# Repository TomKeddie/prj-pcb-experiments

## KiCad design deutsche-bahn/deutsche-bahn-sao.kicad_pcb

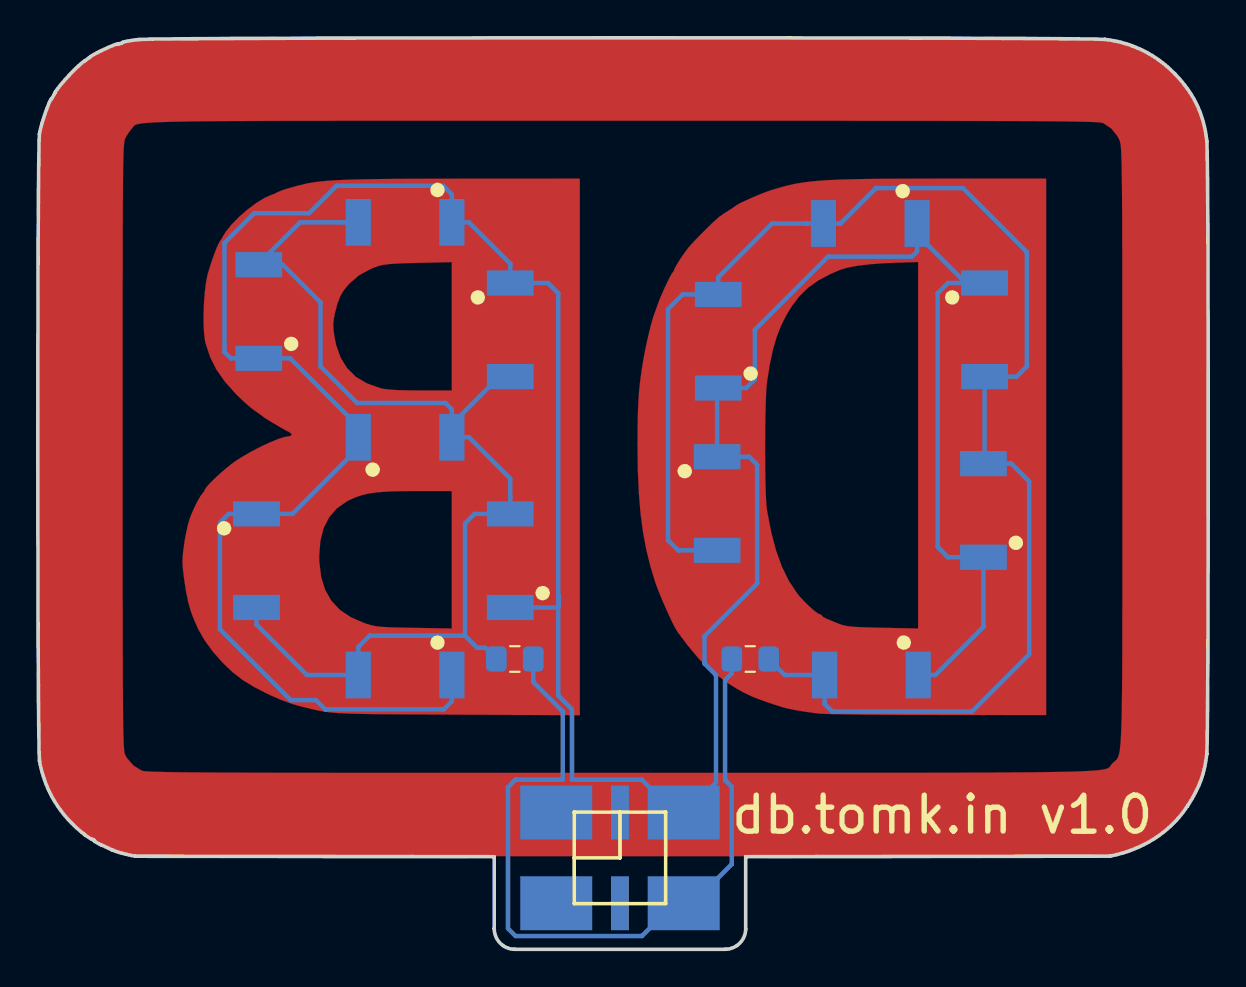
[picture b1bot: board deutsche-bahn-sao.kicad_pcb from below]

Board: 2 copper layers, 65.0 x 50.6 mm, 19 parts (16 on the bottom side), 4 nets.

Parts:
D1, D2, D3, D4, D5, D6, D7, D8, D9, D10, D11, D12, D13: LED; XZM2CYK45WT-9-NOMASK
H1: Logo Copper; 1280px-Deutsche_Bahn_AG-Logo-copper
H2: Logo Mask; 1280px-Deutsche_Bahn_AG-Logo-mask-invert
H3: Logo Silk; 1280px-Deutsche_Bahn_AG-Logo-silk-invert
J1: Conn_02x03_Odd_Even; PinSocket_2x03_P2.54mm_Vertical_SMD_SAO
R1, R2: 47R; C_0805_2012Metric_Pad1.15x1.40mm_HandSolder

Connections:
+3V3: D1.2, D2.2, D3.2, D4.2, D5.2, D6.2, D7.2, D8.2, D9.2, D10.2, D11.2, D12.2, D13.2, J1.5
GND: J1.6, R1.2, R2.2
unnamed: D1.1, D2.1, D4.1, D7.1, D10.1, D11.1, R1.1
unnamed: D3.1, D5.1, D6.1, D8.1, D9.1, D12.1, D13.1, R2.1

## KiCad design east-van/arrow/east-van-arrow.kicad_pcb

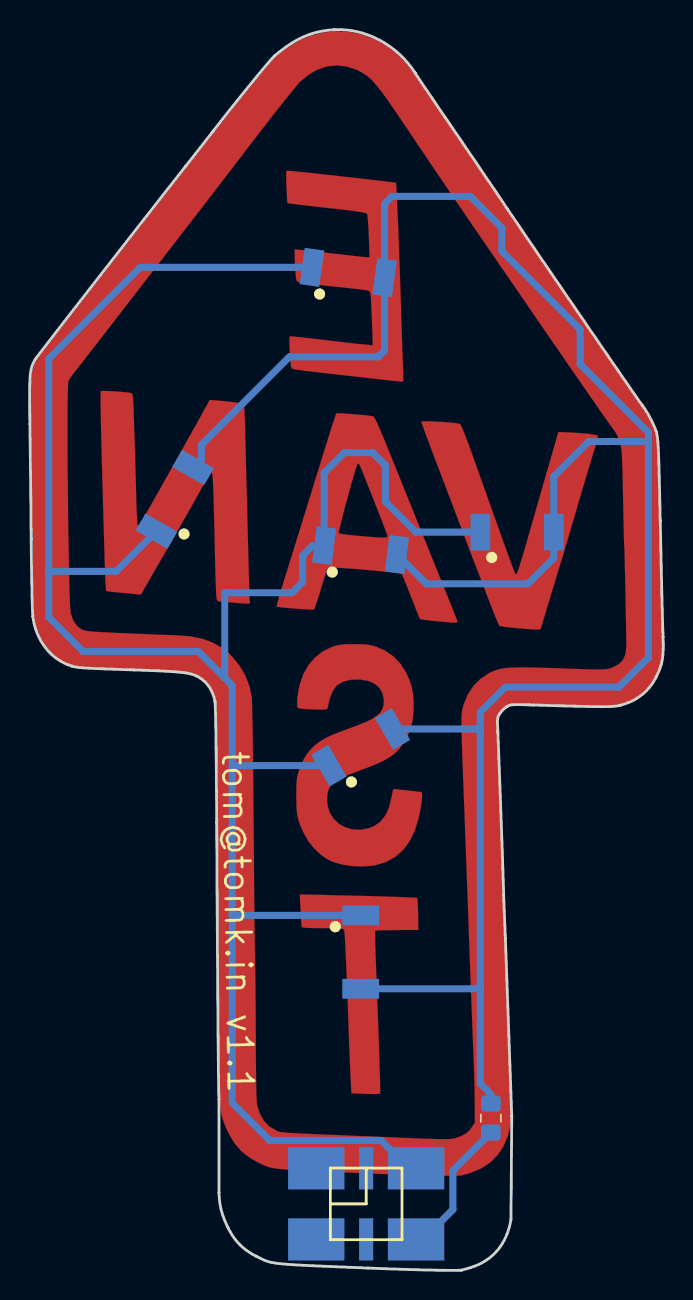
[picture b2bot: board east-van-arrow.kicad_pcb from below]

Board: 2 copper layers, 44.9 x 88.0 mm, 10 parts (8 on the bottom side), 3 nets.

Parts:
D1, D2, D3, D4, D5, D6: LED; XZM2CYK45WT-9-NOMASK
H1: Copper; east-van-arrow-copper
H2: Mask; east-van-arrow-mask-invert
J1: Conn_02x03_Odd_Even; PinSocket_2x03_P2.54mm_Vertical_SMD_SAO
R1: 220R; C_0805_2012Metric_Pad1.15x1.40mm_HandSolder

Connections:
+3V3: D1.2, D2.2, D3.2, D4.2, D5.2, D6.2, J1.5
/CATHODE: D1.1, D2.1, D3.1, D4.1, D5.1, D6.1, R1.1
GND: J1.6, R1.2

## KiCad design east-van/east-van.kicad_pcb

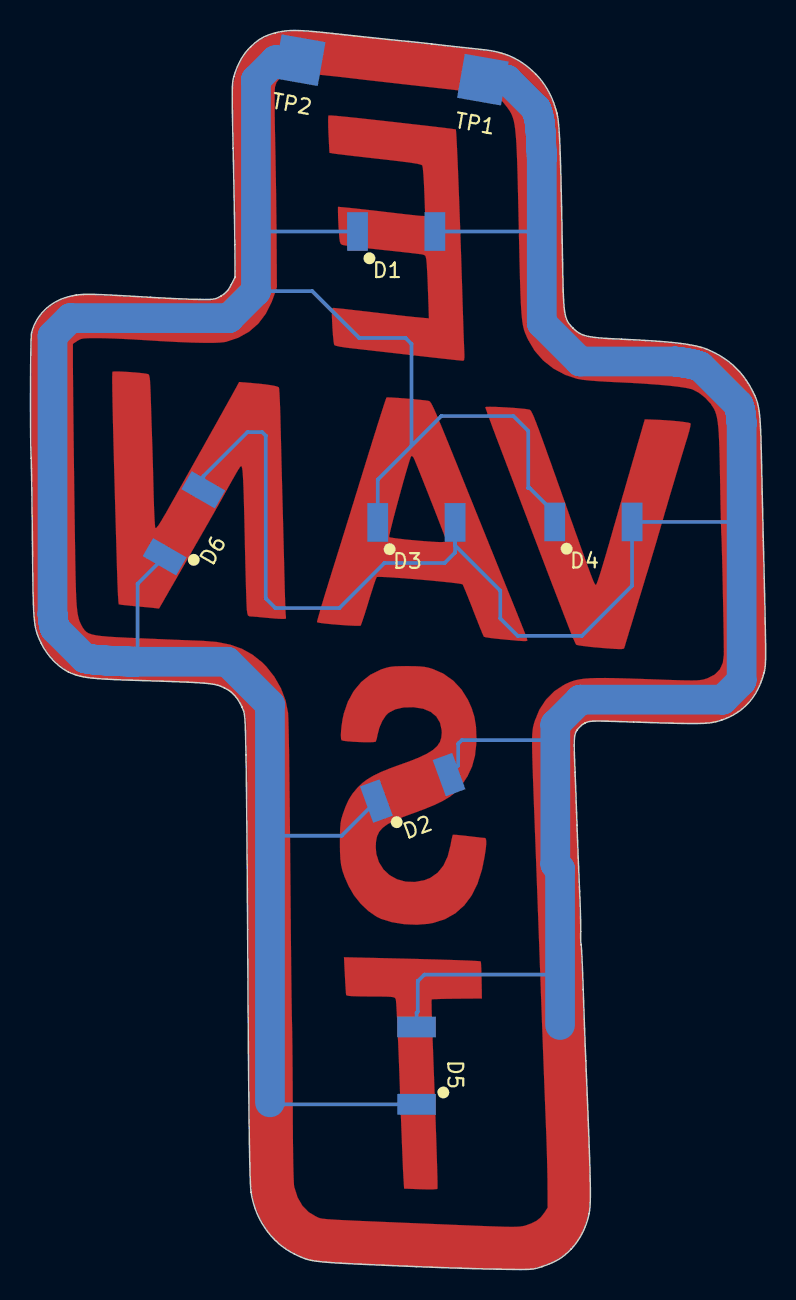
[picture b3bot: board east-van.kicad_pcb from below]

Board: 2 copper layers, 49.4 x 83.3 mm, 11 parts (8 on the bottom side), 2 nets.

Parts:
D1, D2, D3, D4, D5, D6: Device_LED; XZM2CYK45WT-9-NOMASK
H1: mask; east-van-inv-mask
H2: silk; east-van-silk
H3: copper; east-van-copper
TP1, TP2: TestPoint; Measurement_Point_Square-SMD-Pad_Big

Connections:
/A: D1.2, D2.2, D3.2, D4.2, D5.2, D6.2, TP2.1
/C: D1.1, D2.1, D3.1, D4.1, D5.1, D6.1, TP1.1

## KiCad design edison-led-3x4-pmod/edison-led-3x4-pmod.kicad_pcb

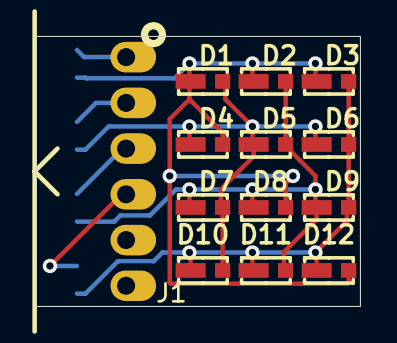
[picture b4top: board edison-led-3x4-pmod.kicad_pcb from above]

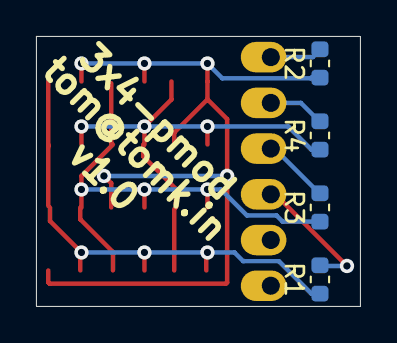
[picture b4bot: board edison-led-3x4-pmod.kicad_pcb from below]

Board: 2 copper layers, 18.0 x 15.0 mm, 17 parts (4 on the bottom side), 8 nets.

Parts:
D1, D2, D3, D4, D5, D6, D7, D8, D9, D10, D11, D12: LED; EDISON-3014
J1: PMOD-1x6-MALE; PMOD_1X6_PTH_RA_PLUG
R1, R2, R3, R4: 47R; R_0603_1608Metric

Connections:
D0: D1.2, D2.2, D3.2, D4.1, D8.1, D12.1, R2.1
D1: D1.1, D4.2, D5.2, D6.2, D7.1, D10.1, R4.1
D2: D2.1, D5.1, D7.2, D8.2, D9.2, D11.1, R3.1
D3: D3.1, D6.1, D9.1, D10.2, D11.2, D12.2, R1.1
unnamed: J1.1, R2.2
unnamed: J1.2, R4.2
unnamed: J1.3, R3.2
unnamed: J1.4, R1.2

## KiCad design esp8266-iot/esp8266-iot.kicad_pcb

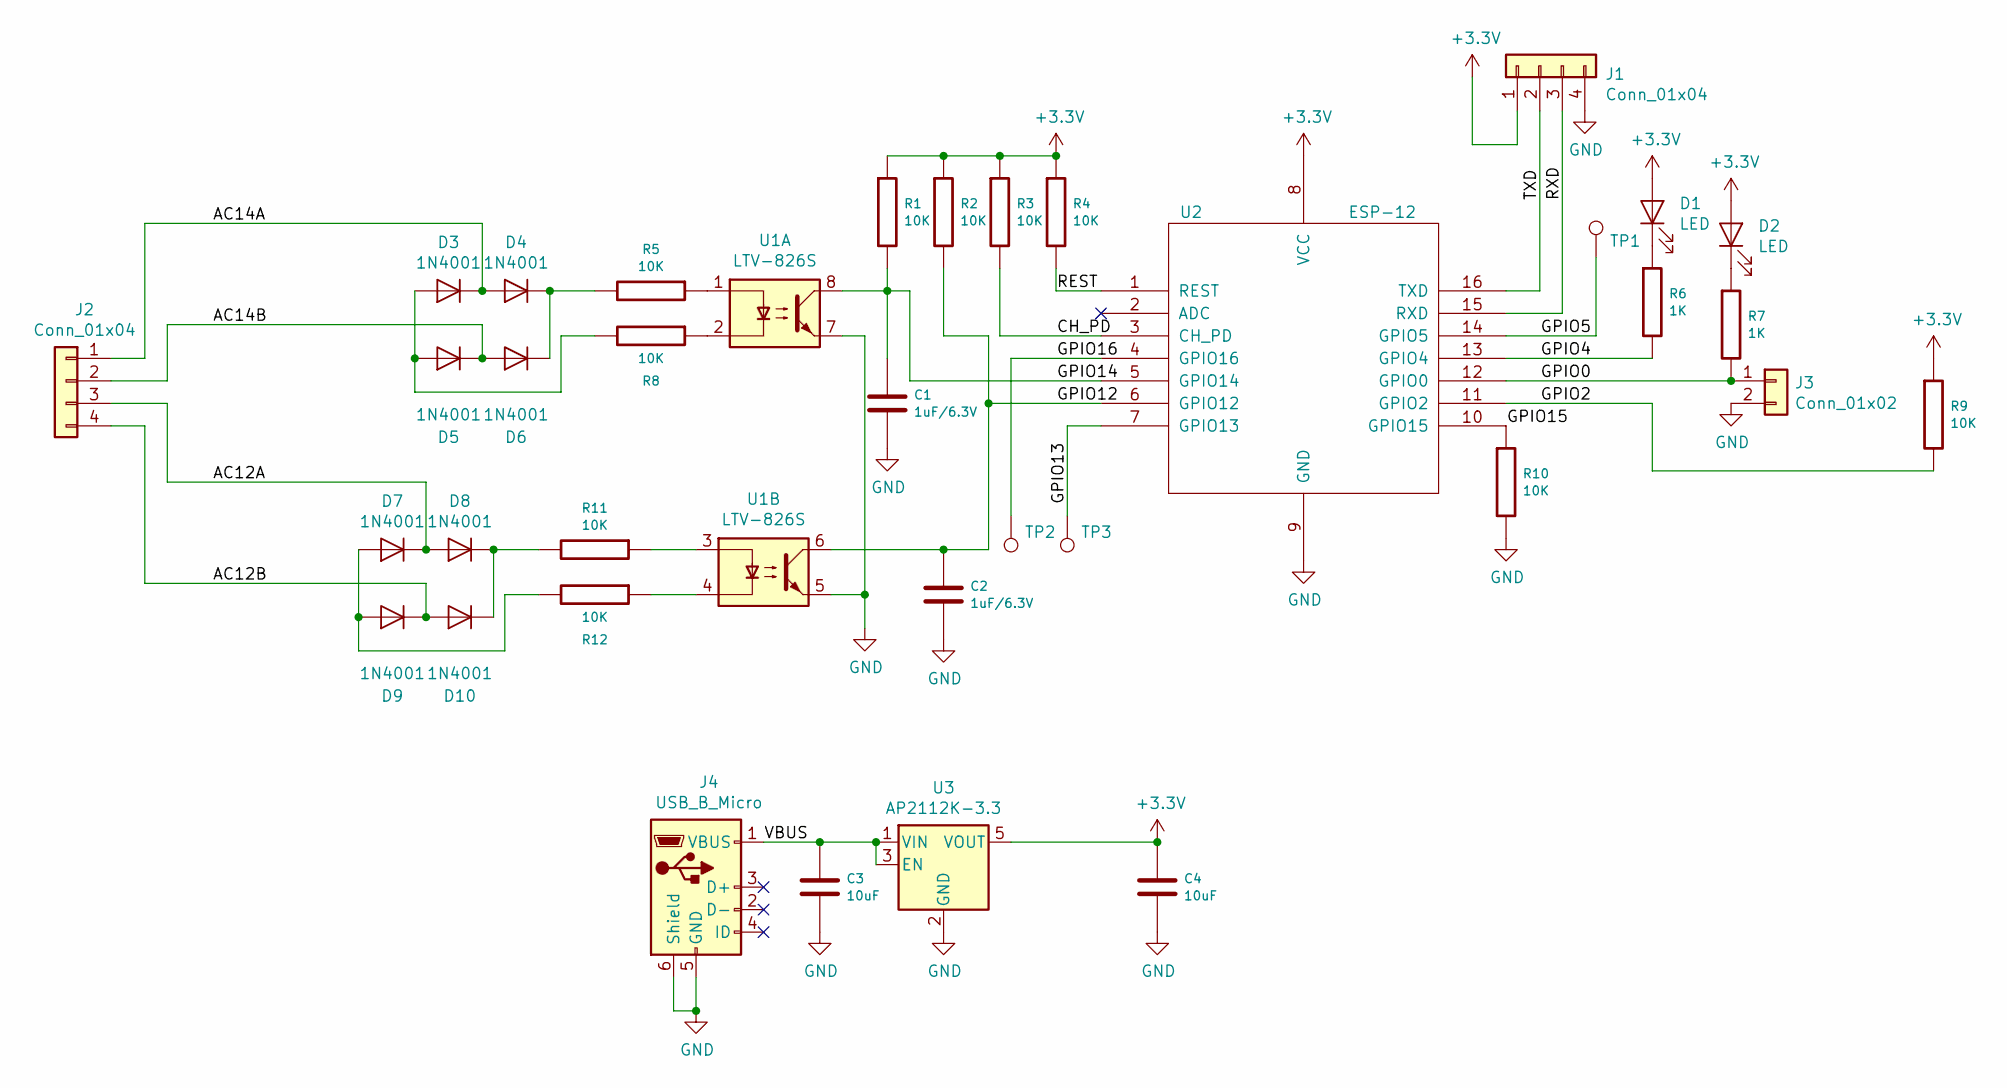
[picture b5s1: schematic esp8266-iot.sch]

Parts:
C1, C2: 1uF/6.3V; C_1206_3216Metric
C3, C4: 10uF; C_1206_3216Metric
D1, D2: LED; LED_0805_2012Metric
D3, D4, D5, D6, D7, D8, D9, D10: 1N4001; D_SMA; Digikey 641-1156-1-ND
J1: Conn_01x04; PinHeader_1x04_P2.54mm_Vertical
J2: Conn_01x04; PhoenixContact_MC_1,5_4-G-5.08_1x04_P5.08mm_Horizontal
J3: Conn_01x02; PinHeader_1x02_P2.54mm_Vertical
J4: USB_B_Micro; USB_MICRO_TAOBAO_SMD_PTH
R1, R2, R3, R4, R5, R8, R9, R10, R11, R12: 10K; C_0805_2012Metric
R6, R7: 1K; C_0805_2012Metric
TP1, TP2, TP3: TestPoint; TestPoint_Pad_D3.0mm
U1: LTV-826S; DIP-8_W8.89mm_SMDSocket_LongPads
U2: ESP-12; ESP-12E_SMD
U3: AP2112K-3.3; SOT-23-5

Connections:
+3V3: C4.1, D1.2 (A), D2.2 (A), J1.1, R1.1, R2.1, R3.1, R4.1, R9.1, U2.8 (VCC), U3.5 (VOUT)
/AC12A: D7.1 (K), D8.2 (A), J2.3
/AC12B: D9.1 (K), D10.2 (A), J2.4
/AC14A: D3.1 (K), D4.2 (A), J2.1
/AC14B: D5.1 (K), D6.2 (A), J2.2
/CH_PD: R3.2, U2.3 (CH_PD)
/GPIO0: J3.1, R7.2, U2.12 (GPIO0)
/GPIO2: R9.2, U2.11 (GPIO2)
/GPIO4: R6.2, U2.13 (GPIO4)
/GPIO5: TP1.1, U2.14 (GPIO5)
/GPIO12: C2.1, R2.2, U1.6, U2.6 (GPIO12)
/GPIO13: TP3.1, U2.7 (GPIO13)
/GPIO14: C1.1, R1.2, U1.8, U2.5 (GPIO14)
/GPIO15: R10.1, U2.10 (GPIO15)
/GPIO16: TP2.1, U2.4 (GPIO16)
/REST: R4.2, U2.1 (REST)
/RXD: J1.3, U2.15 (RXD)
/TXD: J1.2, U2.16 (TXD)
/VBUS: C3.1, J4.1 (VBUS), U3.1 (VIN), U3.3 (EN)
GND: C1.2, C2.2, C3.2, C4.2, J1.4, J3.2, J4.5 (GND), J4.6 (Shield), R10.2, U1.5, U1.7, U2.9 (GND), U3.2 (GND)
unnamed: D1.1 (K), R6.1
unnamed: D2.1 (K), R7.1
unnamed: D3.2 (A), D5.2 (A), R8.2
unnamed: D4.1 (K), D6.1 (K), R5.2
unnamed: D7.2 (A), D9.2 (A), R12.2
unnamed: D8.1 (K), D10.1 (K), R11.2
unnamed: R5.1, U1.1
unnamed: R8.1, U1.2
unnamed: R11.1, U1.3
unnamed: R12.1, U1.4

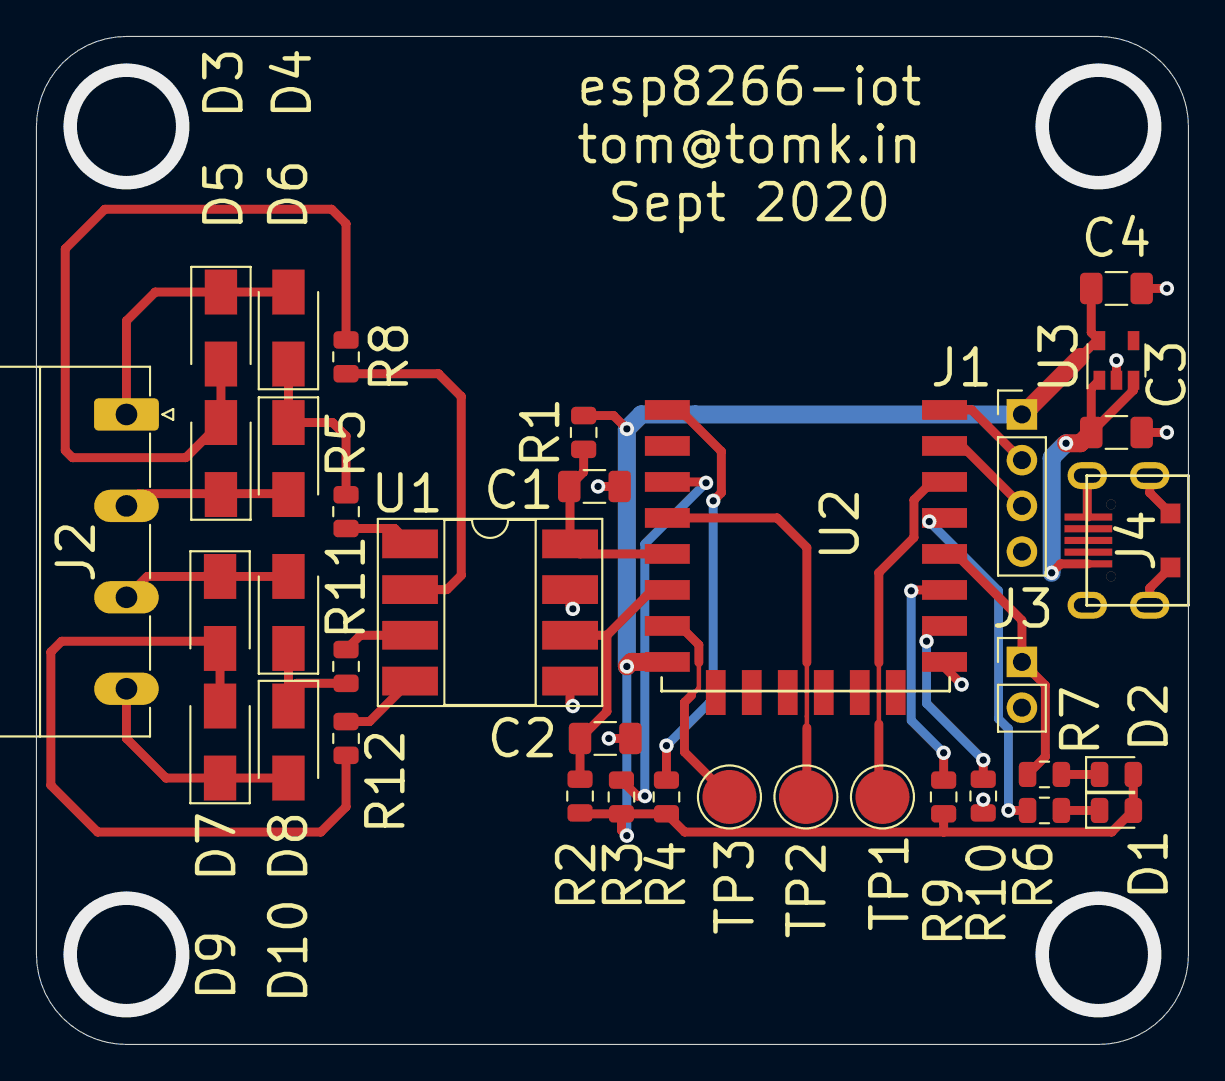
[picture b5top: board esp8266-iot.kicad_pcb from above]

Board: 2 copper layers, 64.0 x 56.0 mm, 36 parts (0 on the bottom side), 30 nets.

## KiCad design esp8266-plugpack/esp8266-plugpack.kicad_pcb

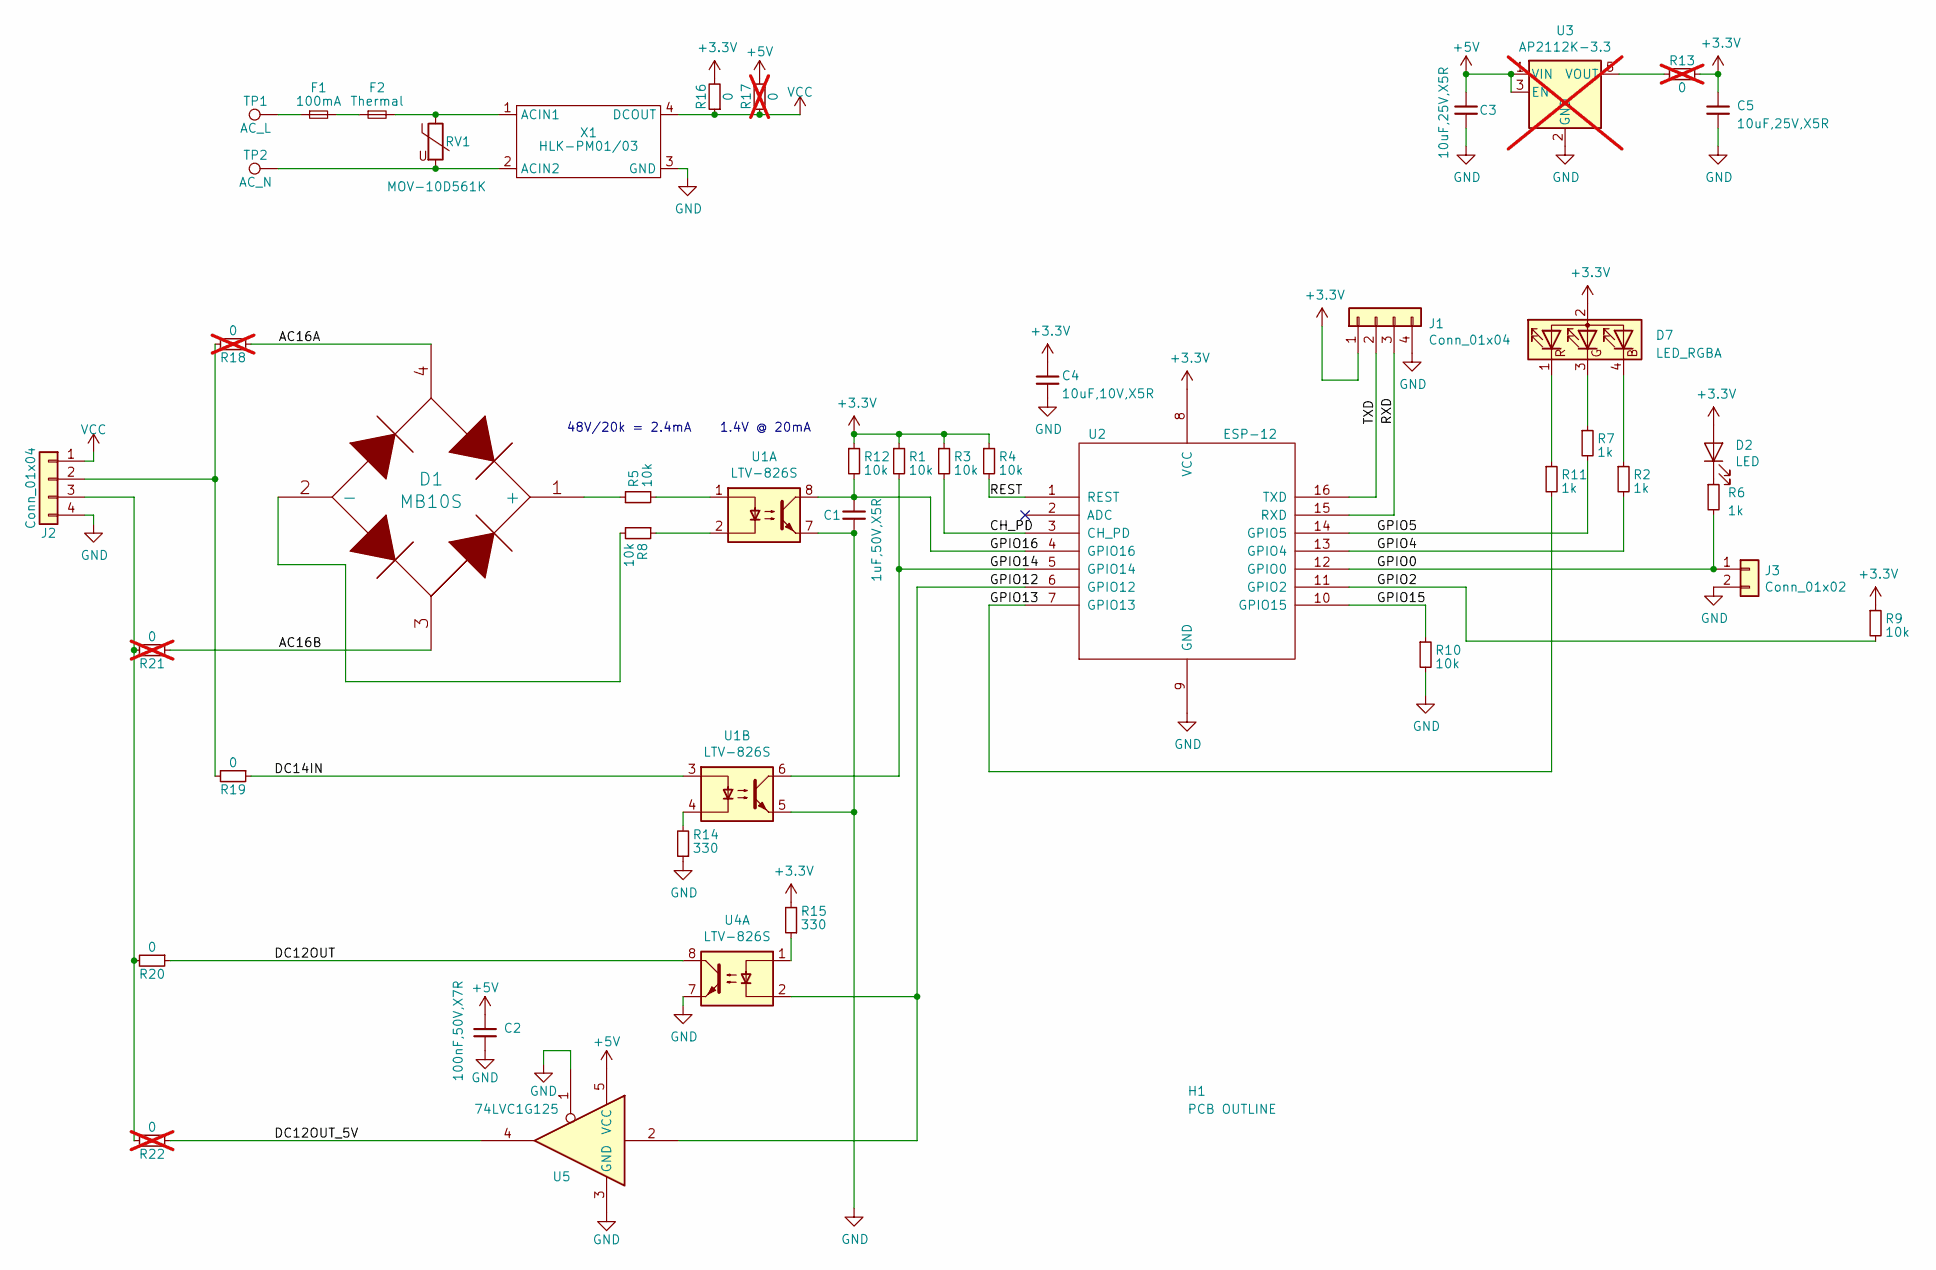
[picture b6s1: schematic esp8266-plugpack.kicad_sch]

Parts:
C1: 1uF,50V,X5R; C_0603_1608Metric; MFGPN CL10A105KB8NNNC; LCSC C15849
C2: 100nF,50V,X7R; C_0603_1608Metric; MFGPN CC0603KRX7R9BB104; LCSC C14663
C3, C5: 10uF,25V,X5R; C_0603_1608Metric; MFGPN CL10A106MA8NRNC; LCSC C96446
C4: 10uF,10V,X5R; C_0603_1608Metric; MFGPN CL10A106KP8NNNC; LCSC C19702
D1: MB10S; Diode_Bridge_MBnnS; LCSC C2488
D2: LED; LED_0805_2012Metric; LCSC C34499
D7: LED_RGBA; LED_D5.0mm-4_RGB
F1: 100mA; Fuse_2410
F2: Thermal; R_Axial_DIN0204_L3.6mm_D1.6mm_P7.62mm_Horizontal
H1: PCB OUTLINE; PCB_ALIEXPRESS_PLUGPACK_1
J1: Conn_01x04; PinHeader_1x04_P2.54mm_Vertical
J2: Conn_01x04; JST_PH_B4B-PH-SM4-TB_1x04-1MP_P2.00mm_Vertical
J3: Conn_01x02; PinHeader_1x02_P2.54mm_Vertical
R1, R3, R4, R5, R8, R9, R10, R12: 10k; R_0603_1608Metric; MFGPN 0603WAF1002T5E; LCSC C25804
R2, R6, R7, R11: 1k; R_0603_1608Metric; MFGPN 0603WAF1001T5E; LCSC C21190
R13, R17, R18, R21, R22: 0; R_0603_1608Metric; MFGPN 0603WAF0000T5E; LCSC C21189; not fitted
R14, R15: 330; R_0603_1608Metric; MFGPN 0603WAF3300T5E; LCSC C23138
R16, R19, R20: 0; R_0603_1608Metric; MFGPN 0603WAF0000T5E; LCSC C21189
RV1: MOV-10D561K; RV_Disc_D12mm_W3.9mm_P7.5mm
TP1: AC_L; TestPoint_Pad_D3.0mm
TP2: AC_N; TestPoint_Pad_D3.0mm
U1, U4: LTV-826S; DIP-8_W8.89mm_SMDSocket_LongPads
U2: ESP-12; ESP-12E_SMD; LCSC C82891
U3: AP2112K-3.3; SOT-23-5; not fitted
U5: 74LVC1G125; SOT-23-5; LCSC C23654
X1: HLK-PM01/03; HLK-PMxx

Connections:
+3.3V: C4.1, C5.1, D2.2 (A), D7.2 (A), J1.1, R1.1, R3.1, R4.1, R9.1, R12.1, R13.2, R15.2, R16.2, U2.8 (VCC)
+5V: C2.1, C3.1, R17.2, U3.1 (VIN), U3.3 (EN), U5.5 (VCC)
/AC16A: D1.4, R18.1
/AC16B: D1.3, R21.1
/CH_PD: R3.2, U2.3 (CH_PD)
/DC12OUT: R20.1, U4.8
/DC12OUT_5V: R22.1, U5.4
/DC14IN: R19.1, U1.3
/GPIO0: J3.1, R6.2, U2.12 (GPIO0)
/GPIO2: R9.2, U2.11 (GPIO2)
/GPIO4: R2.2, U2.13 (GPIO4)
/GPIO5: R7.2, U2.14 (GPIO5)
/GPIO12: U2.6 (GPIO12), U4.2, U5.2
/GPIO13: R11.2, U2.7 (GPIO13)
/GPIO14: R1.2, U1.6, U2.5 (GPIO14)
/GPIO15: R10.1, U2.10 (GPIO15)
/GPIO16: C1.1, R12.2, U1.8, U2.4 (GPIO16)
/REST: R4.2, U2.1 (REST)
/RXD: J1.3, U2.15 (RXD)
/TXD: J1.2, U2.16 (TXD)
GND: C1.2, C2.2, C3.2, C4.2, C5.2, J1.4, J2.4, J3.2, R10.2, R14.1, U1.5, U1.7, U2.9 (GND), U3.2 (GND), U4.7, U5.1, U5.3 (GND), X1.3 (GND)
unnamed: D1.1 (+), R5.1
unnamed: D1.2 (-), R8.2
unnamed: D2.1 (K), R6.1
unnamed: D7.4 (BK), R2.1
unnamed: D7.3 (GK), R7.1
unnamed: D7.1 (RK), R11.1
unnamed: F1.1, TP1.1
unnamed: F1.2, F2.1
unnamed: J2.2, R18.2, R19.2
unnamed: J2.3, R20.2, R21.2, R22.2
unnamed: R5.2, U1.1
unnamed: R8.1, U1.2
unnamed: R14.2, U1.4
unnamed: R15.1, U4.1
unnamed: R13.1, U3.5 (VOUT)
unnamed: F2.2, RV1.1, X1.1 (ACIN1)
unnamed: RV1.2, TP2.1, X1.2 (ACIN2)
VCC: J2.1, R16.1, R17.1, X1.4 (DCOUT)

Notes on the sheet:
48V/20k = 2.4mA
1.4V @ 20mA

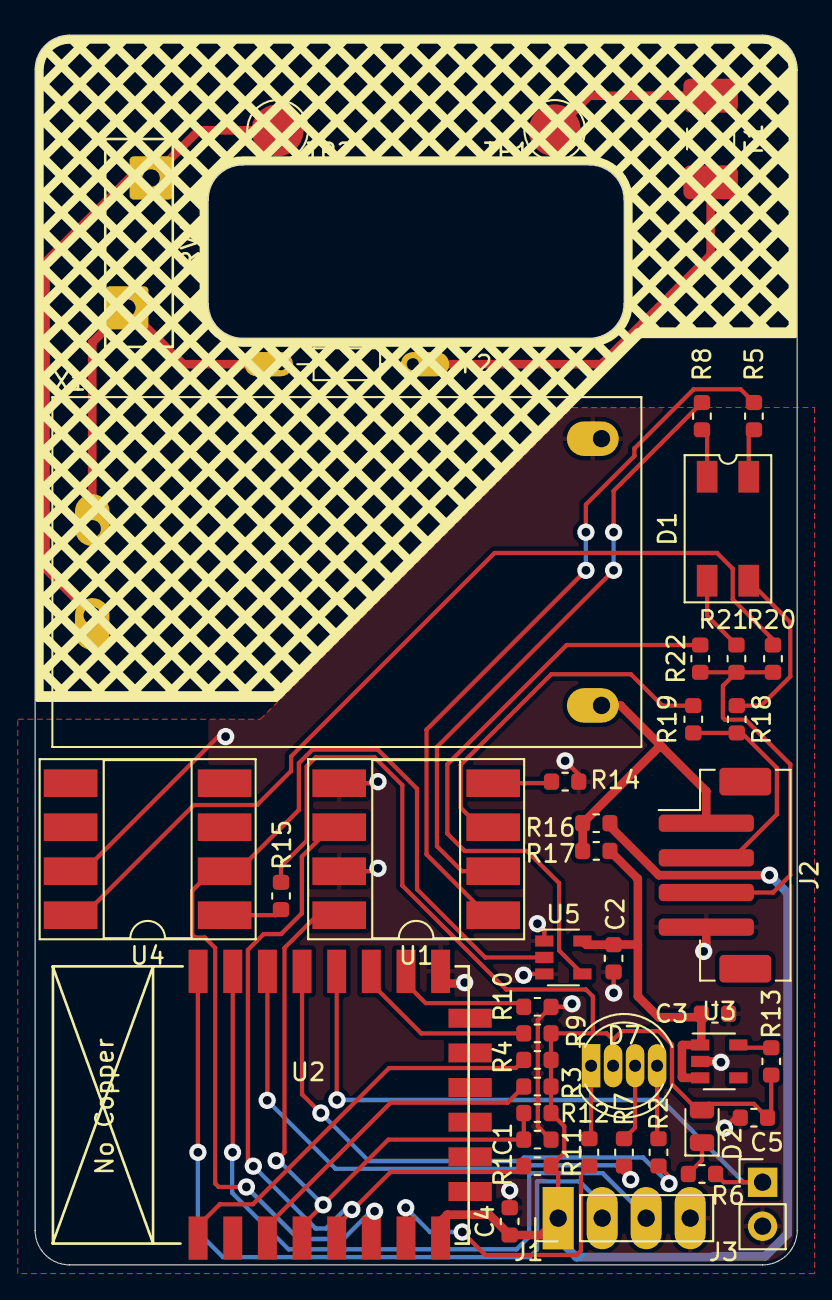
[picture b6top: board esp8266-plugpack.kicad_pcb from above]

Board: 2 copper layers, 44.0 x 71.0 mm, 45 parts (0 on the bottom side), 39 nets.

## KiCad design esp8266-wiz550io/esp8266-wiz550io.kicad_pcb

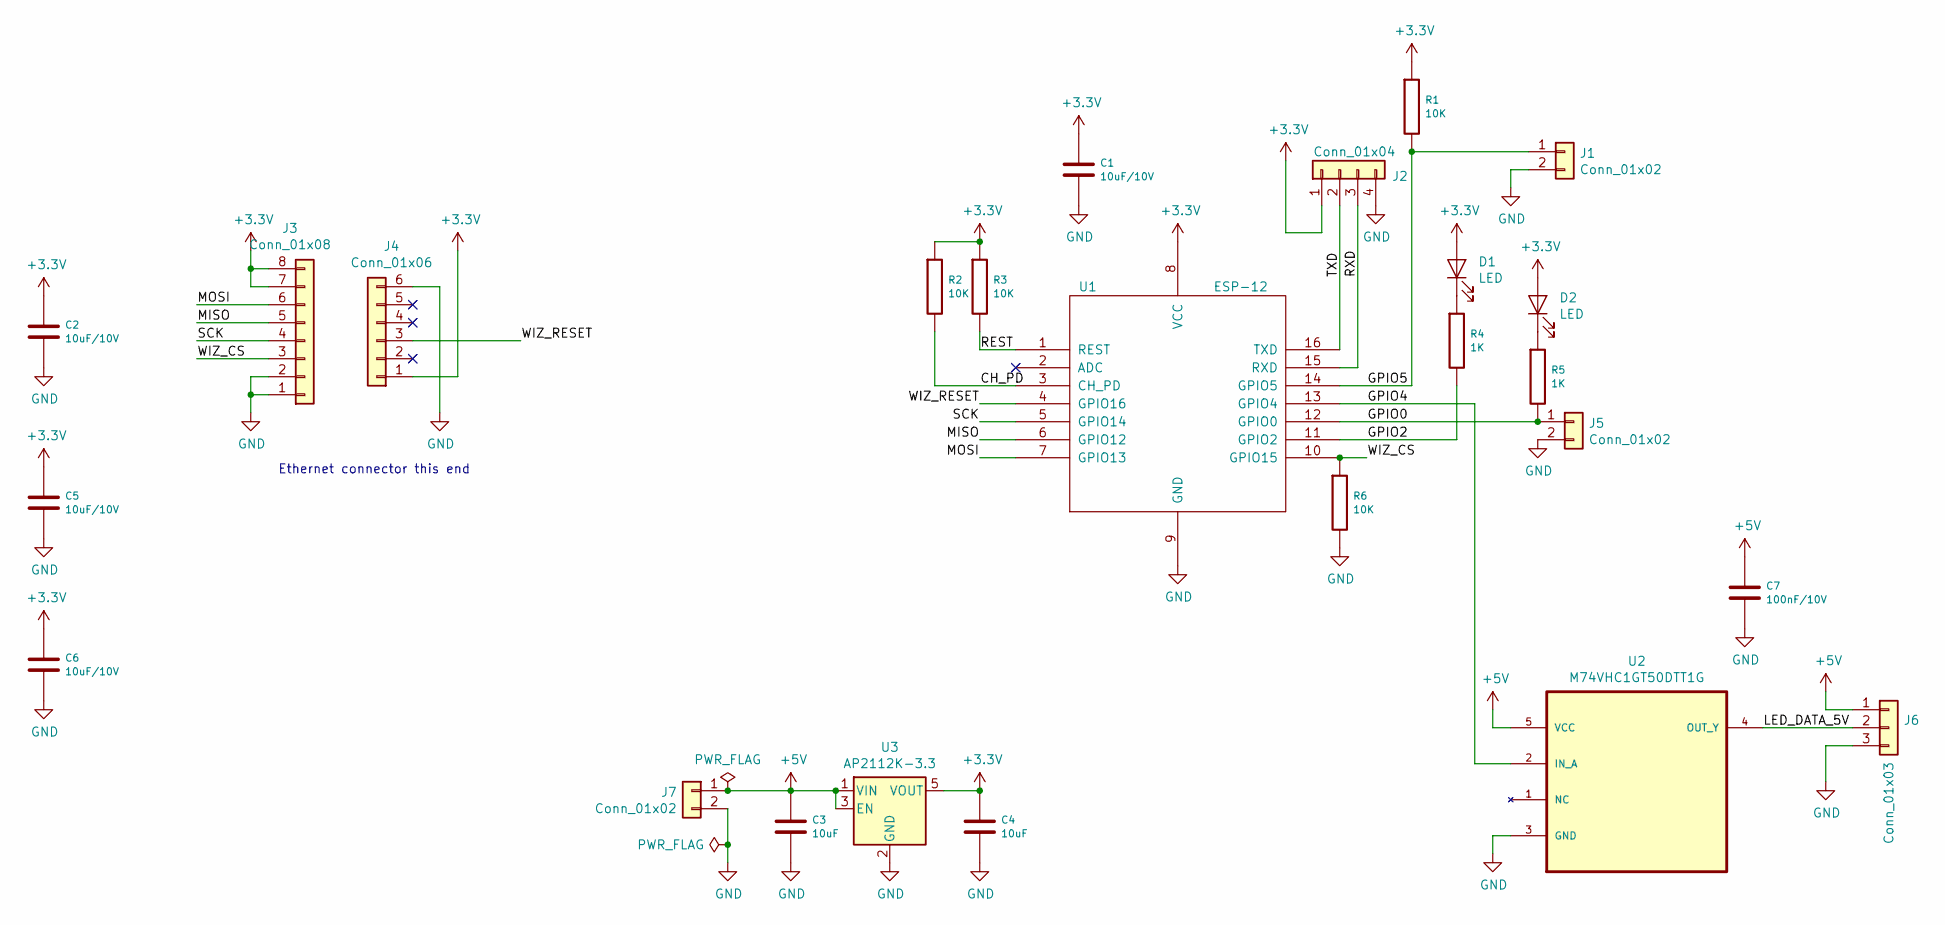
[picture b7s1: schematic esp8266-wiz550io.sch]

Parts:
C1, C2, C5, C6: 10uF/10V; C_0805_2012Metric; LCSC DNP
C3, C4: 10uF; C_0805_2012Metric
C7: 100nF/10V; C_0805_2012Metric; LCSC DNP
D1, D2: LED; LED_0805_2012Metric
J1, J5, J7: Conn_01x02; PinHeader_1x02_P2.54mm_Vertical
J2: Conn_01x04; PinHeader_1x04_P2.54mm_Vertical
J3: Conn_01x08; PinHeader_1x08_P2.54mm_Vertical
J4: Conn_01x06; PinHeader_1x06_P2.54mm_Vertical
J6: Conn_01x03; PinHeader_1x03_P2.54mm_Vertical
R1, R2, R3, R6: 10K; C_0805_2012Metric
R4, R5: 1K; C_0805_2012Metric
U1: ESP-12; ESP-12E_SMD
U2: M74VHC1GT50DTT1G; SOT95P275X110-5N; MPN M74VHC1GT50DTT1G
U3: AP2112K-3.3; SOT-23-5

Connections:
+3V3: C1.1, C2.1, C4.1, C5.1, C6.1, D1.2 (A), D2.2 (A), J2.1, J3.7, J3.8, J4.1, R1.1, R2.1, R3.1, U1.8 (VCC), U3.5 (VOUT)
+5V: C3.1, C7.1, J6.1, J7.1, U2.5 (VCC), U3.1 (VIN), U3.3 (EN)
/CH_PD: R2.2, U1.3 (CH_PD)
/GPIO0: J5.1, R5.2, U1.12 (GPIO0)
/GPIO2: R4.2, U1.11 (GPIO2)
/GPIO4: U1.13 (GPIO4), U2.2 (IN_A)
/GPIO5: J1.1, R1.2, U1.14 (GPIO5)
/LED_DATA_5V: J6.2, U2.4 (OUT_Y)
/MISO: J3.5, U1.6 (GPIO12)
/MOSI: J3.6, U1.7 (GPIO13)
/REST: R3.2, U1.1 (REST)
/RXD: J2.3, U1.15 (RXD)
/SCK: J3.4, U1.5 (GPIO14)
/TXD: J2.2, U1.16 (TXD)
/WIZ_CS: J3.3, R6.1, U1.10 (GPIO15)
/WIZ_RESET: J4.3, U1.4 (GPIO16)
GND: C1.2, C2.2, C3.2, C4.2, C5.2, C6.2, C7.2, J1.2, J2.4, J3.1, J3.2, J4.6, J5.2, J6.3, J7.2, R6.2, U1.9 (GND), U2.3 (GND), U3.2 (GND)
unnamed: D1.1 (K), R4.1
unnamed: D2.1 (K), R5.1

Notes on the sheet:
Ethernet connector this end

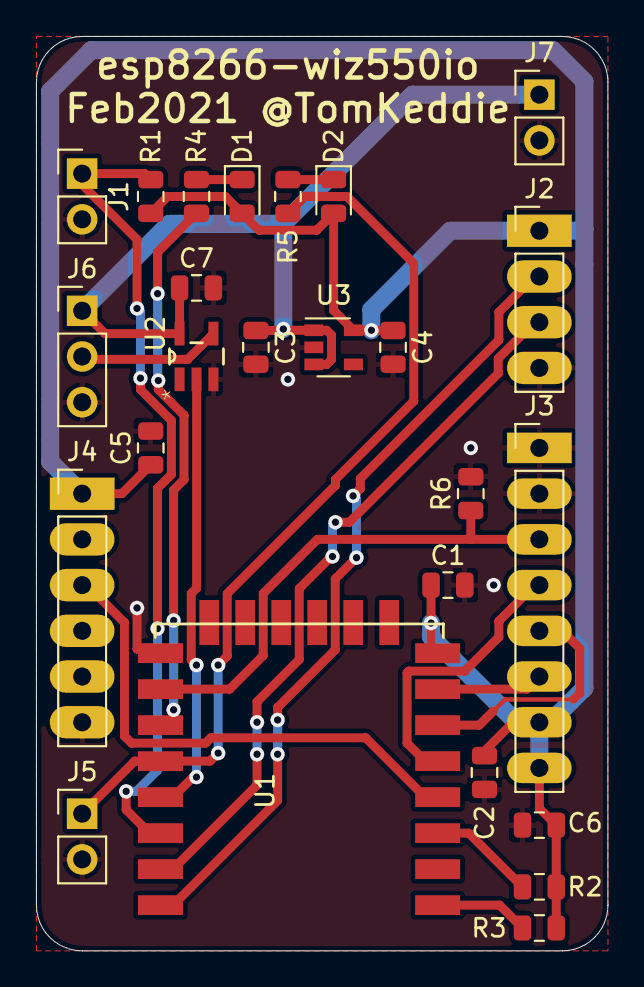
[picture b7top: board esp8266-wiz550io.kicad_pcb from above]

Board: 2 copper layers, 31.8 x 50.8 mm, 25 parts (0 on the bottom side), 19 nets.
